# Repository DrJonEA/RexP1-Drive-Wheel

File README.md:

# RexP1-Drive-Wheel

Drive wheel for my RexP1 Astro Droid Project based on a RP2040Zero board. This Repo repreents the drive wheel subsystem for RexP1.

Checkout the [videos guides](https://www.youtube.com/playlist?list=PLspDyukWAtRUPNdlktaOdk7os9TfTEFh1) to the project over on my [YouTube Channel DrJonEA](https://youtube.com/@drjonea).
 
## RexP1 Intro
RexP1 is a reimagined Star War's inspired Astro Droid based on the R series Droids. It is based on Raspberry PI 5, RP2040 and RP2350 boards. It's control system is a distributed net based on ROS2 and MicroROS frameworks.

All my work on RexP1 is available to  my sponsors. That includes not just this submodule but all the submodules, the build instructions, PCB designs, STL files, CAD designs and most important acess to me to ask questions. Take a look at the sponsorship button on the github repo.

## The Repo
This repo includes the PCB design for the drive wheels and assoicated documentation. It also includes the firmware for a RP2040Zero which acts as a ROS2 Node to control the Wheel and some other sensors.

## Libraries
Note libraries have not been included as submodules in this repo. That is because I wanted just a single copy of the libraries in the master repo for RexP1. So take note of the [lib documentation](docs/Libraries.md).

## Build process
The firmware should build like most *complex* Pico SDK firmware projects. Normal procedure:
```
mkdir build
cd build
cmake ..
make
```
If you have ninja use that instead of make for Windows. Just make sure you update the CMakelists.txt to point to your libraries and that the environment variable PICO_SDK_PATH is defined to point to the SDK.

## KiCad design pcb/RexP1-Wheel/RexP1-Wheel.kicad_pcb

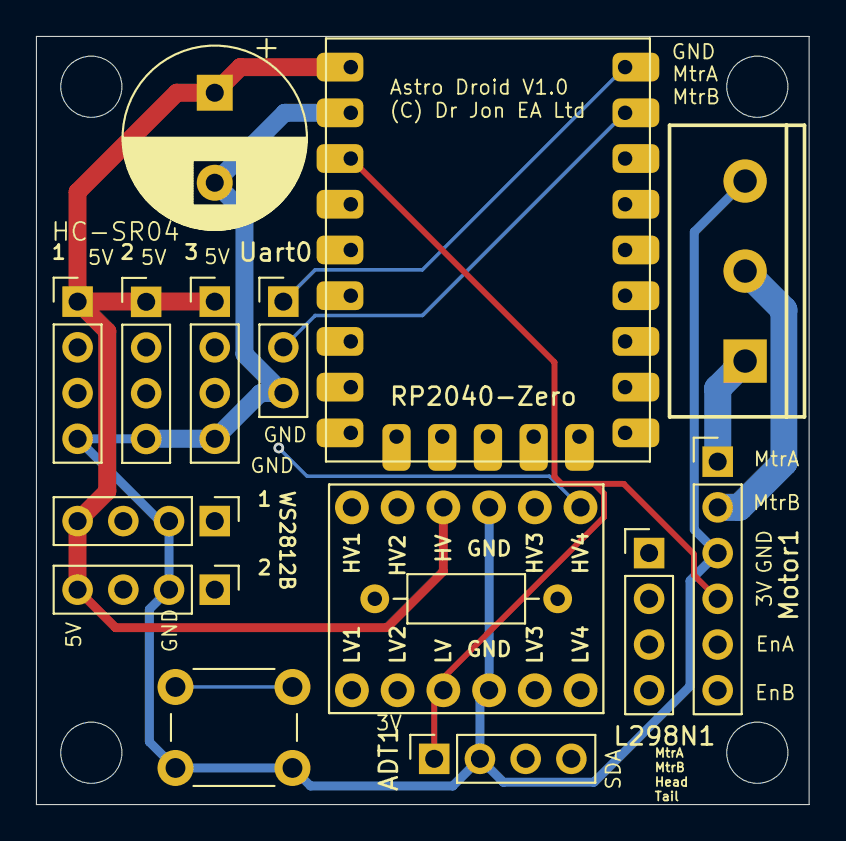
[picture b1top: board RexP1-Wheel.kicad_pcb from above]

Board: 4 copper layers, 42.9 x 42.7 mm, 15 parts (0 on the bottom side), 29 nets.

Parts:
ADT1: Conn_01x04_Socket; PinSocket_1x04_P2.54mm_Vertical
B1: SPARKFUN_LOGIC_LEVEL_CONVERTER
C1: 470uF; CP_Radial_D10.0mm_P5.00mm
HCSR04-1, HCSR04-2, HCSR04-3: Conn_01x04_Pin; PinHeader_1x04_P2.54mm_Vertical
J2: Screw_Terminal_01x03; SCREWTERMINAL-5MM-3
J3: Uart0; PinHeader_1x03_P2.54mm_Vertical
L298N1: Conn_01x04_Pin; PinHeader_1x04_P2.54mm_Vertical
Motor1: Conn_01x06_Pin; PinHeader_1x06_P2.54mm_Vertical
R1: 220R; R_Axial_DIN0207_L6.3mm_D2.5mm_P10.16mm_Horizontal
RZ1: RP2040-Zero
SW1: SW_SPST; SW_PUSH_6mm_H8.5mm
WS2812B-1, WS2812B-2: Conn_01x04_Pin; PinHeader_1x04_P2.54mm_Vertical

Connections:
+3V3: ADT1.1 (VCC), B1.LV, Motor1.4 (VCC), RZ1.30 (3V3)
+5V: B1.HV, C1.1, HCSR04-1.1 (VCC), HCSR04-2.1 (VCC), HCSR04-3.1 (VCC), RZ1.32 (5V), WS2812B-1.4 (VDD), WS2812B-2.4 (VDD)
/Echo-1: B1.LV2 (LV_RXO_1), RZ1.12 (GP12)
/Echo-2: B1.LV3 (LV_RXO_2), RZ1.11 (GP11)
/Echo-3: B1.LV4 (LV_TXI_2), RZ1.10 (GP10)
/Echo-HV-1: B1.HV2 (HV_RXI_1), HCSR04-1.3 (Echo)
/Echo-HV-2: B1.HV3 (HV_RXI_2), HCSR04-2.3 (Echo)
/Echo-HV-3: B1.HV4 (HV_TXO_2), HCSR04-3.3 (Echo)
/EncA: Motor1.5 (EncoderA), RZ1.5 (GP5)
/EncB: Motor1.6 (EncoderB), RZ1.4 (GP4)
/Headlight: L298N1.3 (IN3), RZ1.7 (GP7)
/MtrA: L298N1.1 (IN1), RZ1.3 (GP3)
/MtrB: L298N1.2 (IN2), RZ1.2 (GP2)
/SCL: ADT1.3 (SCL), RZ1.9 (GP9)
/SDA: ADT1.4 (SDA), RZ1.8 (GP8)
/Taillight: L298N1.4 (IN4), RZ1.6 (GP6)
/Trigger-1: HCSR04-1.2 (Trig), RZ1.27 (GP27)
/Trigger-2: HCSR04-2.2 (Trig), RZ1.26 (GP26)
/Trigger-3: HCSR04-3.2 (Trig), RZ1.15 (GP15)
/WS2812B: B1.LV1 (LV_TXI_1), RZ1.13 (GP13)
/sw: RZ1.14 (GP14), SW1.2 (B)
GND: ADT1.2 (GND), B1.GND1 (GND), B1.GND2 (GND), C1.2, HCSR04-1.4 (GND), HCSR04-2.4 (GND), HCSR04-3.4 (GND), J2.3 (GND), J3.3 (GND), Motor1.3 (GND), RZ1.31 (GND), SW1.1 (A), WS2812B-1.2 (Gnd), WS2812B-2.2 (Gnd)
unnamed: B1.HV1 (HV_TXO_1), R1.1
unnamed: J2.2 (MtrPwrB), Motor1.2 (Mtr_PwrB)
unnamed: J2.1 (Mtr_PwrA), Motor1.1 (Mtr_PwrA)
unnamed: J3.2 (RX), RZ1.1 (GP1)
unnamed: J3.1 (TX), RZ1.0 (GP0)
unnamed: R1.2, WS2812B-1.3 (In)
unnamed: WS2812B-1.1 (Out), WS2812B-2.3 (In)

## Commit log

2025-07-14 Moving to new home.
